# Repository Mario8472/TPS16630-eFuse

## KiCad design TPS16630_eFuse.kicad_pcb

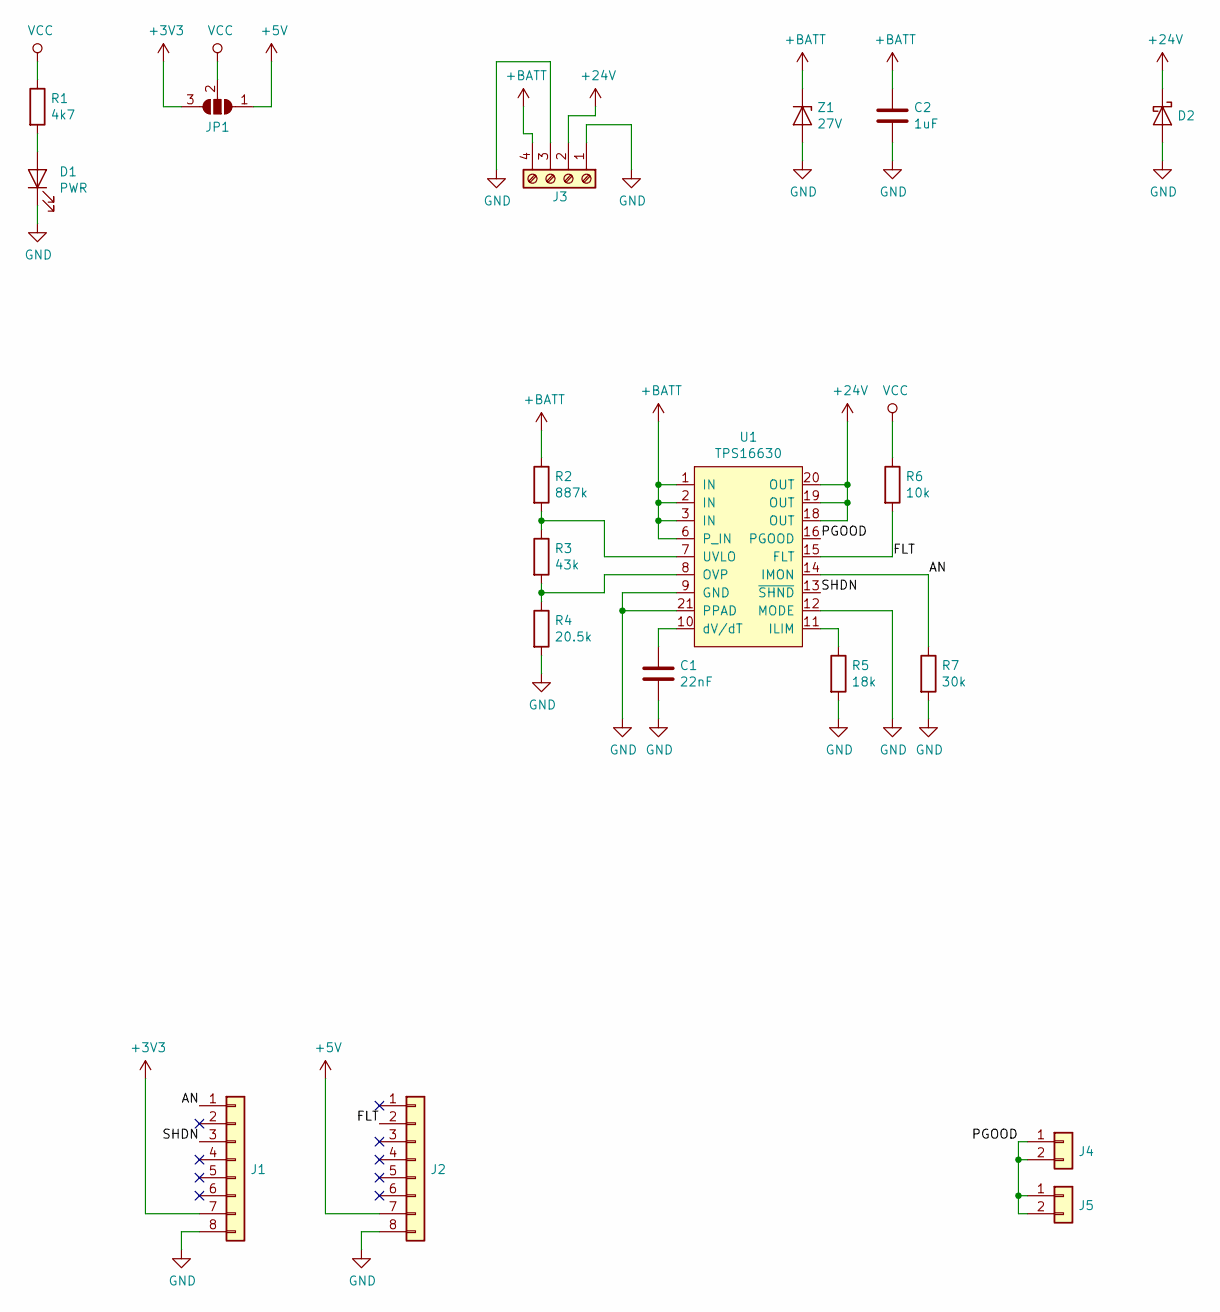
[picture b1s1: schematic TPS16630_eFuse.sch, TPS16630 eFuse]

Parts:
C1: 22nF; C_0805_2012Metric
C2: 1uF; C_1206_3216Metric
D1: PWR; LED_0805_2012Metric
D2: D_Schottky; D_SMA
J1, J2: Conn_01x08; PinHeader_1x08_P2.54mm_Vertical
J3: Screw_Terminal_01x04; PCB_Screw_Terminal_5.08_4ways
J4, J5: Conn_01x02; PinHeader_1x02_P2.54mm_Vertical
JP1: SolderJumper_3_Open; Jumper_0805
R1: 4k7; R_0805_2012Metric
R2: 887k; R_0805_2012Metric
R3: 43k; R_0805_2012Metric
R4: 20.5k; R_0805_2012Metric
R5: 18k; R_0805_2012Metric
R6: 10k; R_0805_2012Metric
R7: 30k; R_0805_2012Metric
U1: TPS16630; ETSSOP-20-1EP_4.4x6.5mm_P0.65mm_EP3x4.2mm
Z1: 27V; D_SMA

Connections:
+3V3: J1.7, JP1.3 (B)
+5V: J2.7, JP1.1 (A)
+24V: D2.1 (K), J3.2, U1.18 (OUT), U1.19 (OUT), U1.20 (OUT)
+BATT: C2.1, J3.4, R2.1, U1.1 (IN), U1.2 (IN), U1.3 (IN), U1.6 (P_IN), Z1.1 (K)
/AN: J1.1, R7.1, U1.14 (IMON)
/FLT: J2.2, R6.2, U1.15 (FLT)
/PGOOD: J4.1, J4.2, J5.1, J5.2, U1.16 (PGOOD)
/SHDN: J1.3, U1.13 (~SHND)
GND: C1.2, C2.2, D1.1 (K), D2.2 (A), J1.8, J2.8, J3.1, J3.3, R4.2, R5.2, R7.2, U1.9 (GND), U1.12 (MODE), U1.21 (PPAD), Z1.2 (A)
unnamed: C1.1, U1.10 (dV/dT)
unnamed: D1.2 (A), R1.2
unnamed: R2.2, R3.1, U1.7 (UVLO)
unnamed: R3.2, R4.1, U1.8 (OVP)
unnamed: R5.1, U1.11 (ILIM)
VCC: JP1.2 (C), R1.1, R6.1

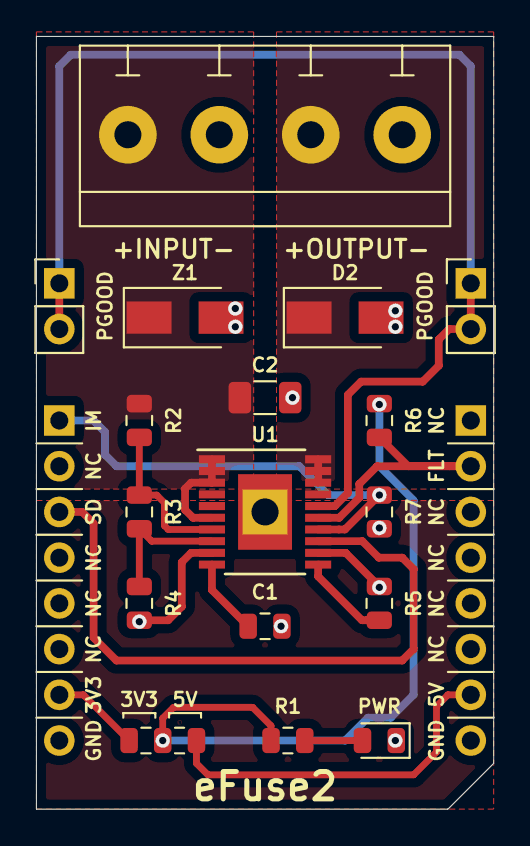
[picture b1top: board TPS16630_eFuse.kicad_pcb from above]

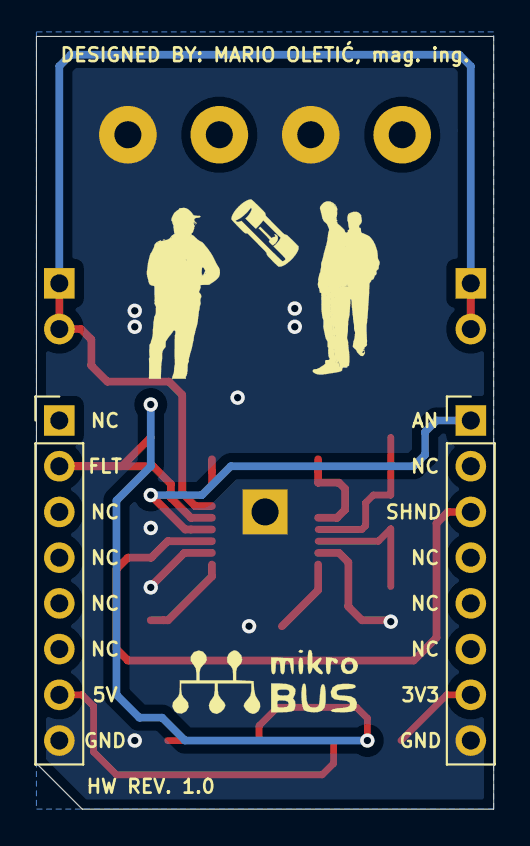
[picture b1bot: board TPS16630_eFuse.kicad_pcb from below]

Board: 2 copper layers, 25.4 x 42.9 mm, 19 parts (2 on the bottom side), 15 nets.
